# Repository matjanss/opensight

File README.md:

# OpenSights

An ESP32 (NodeMCU-32S) that talks Bluetooth LE to a desktop app written in Rust.

- **firmware/** — PlatformIO project for the ESP32
- **app/** — Rust/egui desktop app (Linux, macOS, Windows)
- **protocol/PROTOCOL.md** — the BLE protocol both sides implement
- **hardware/** — KiCad projects for the sensor hardware

Open `esp-sensor.code-workspace` in VS Code: PlatformIO picks up `firmware/` and
rust-analyzer picks up `app/`.

## What it does

- The sensor is the prototype of an electronic target: an acoustic target that locates
  each shot from the sound arriving at its microphones (being built, see
  [PLAN.md](PLAN.md) and [firmware/MEASUREMENT.md](firmware/MEASUREMENT.md)). Until the
  measuring hardware is running, a short press on BOOT makes a random test shot.
- The app shows the shots on a 10 m air pistol card and scores them: whole rings with X for an inner ten, or decimals (a setting). The series
  list and total sit next to the card.
- No shot is lost when the link drops or the sensor restarts: it keeps its shots in flash
  (about 2,000 of them) and resends the ones the app missed.
- A shot the sensor heard but couldn't measure (a second shot too soon after another), or
  one only the light curtain saw (through an existing hole), is listed in the series as
  "not scored", with a notice on the card: check the paper card for those. Click one (in
  the list or on the notice) to resolve it: place it on the card (click the hole, drag the
  shot until it fits, or type x and y), mark it the same hole as another shot, or count it a
  miss (0). It then takes its place in the series, marked "by hand", and can be changed or
  put back to "not scored" by selecting it.
- The app can save every event the sensor captured (also the rejected ones) to a log file,
  one per day, in the same format as the sensor's serial log (Settings → Measurement; on by
  default). Settings also show the sensor's calibration, settings and air readings.
- Settings → Measurement → **A shot needs the IR curtain's confirmation** switches the light
  curtain's check on the sensor on or off. Off, the sound alone decides what counts as a
  shot (the curtain's lights are off too, and no shots through an existing hole are
  reported). On again, it uses the window last set (45–100 µs if none was).
- Settings → Measurement → **Change the settings…** edits the sensor's measuring settings:
  the solver's limits, the curtain's window, the mic span, the dead time and the channels.
  Values out of range can't be written; the sensor's own check has the last word, and the
  app says when it didn't take them.
- Settings → **Shot highlight color** (blue or red): the ring drawn around the shot you
  click, and around the holes found in a card photo.
- The notices on the card (close calls, hits not scored) minimise with the bar at their top
  right, to just "!" and a short title; click that to open them again.
- Click on shots that overlap (a tight group, two shots through one hole) to get a list of
  them all; pick one to see its details.
- Calibrate from the app: Settings → Measurement → **Calibrate…** walks through the spark
  points of the calibration template (16 points, 10 sparks each), fits the microphones'
  positions and timing, shows the result, and writes it to the sensor. **Field check…** makes
  a few sparks at the template's centre and tells you whether the calibration still holds.
- **Take photo** (under the series): a photo of the shot card, taken with a phone, shows
  under the shots, and the app compares each shot with its hole (the sensor's accuracy).
  The series list then shows each shot's score on the paper beside the sensor's; **Card
  details** shows it all (the sensor against the holes per shot, warnings, shots per ring).
  **Finished** on the phone's page closes the app's link.
  Scan the QR code with the phone (on the same Wi-Fi), take the photo with the card flat and
  the phone straight above it. The photo's metadata (location and the like) is removed;
  photos are kept 30 days unless marked to keep. Work in progress, see
  [app/CARDPHOTO.md](app/CARDPHOTO.md).
- **Count cards** (the mode buttons at the top of the right column switch between
  **Shoot series** and **Count cards**; with or without a sensor): scores paper cards from
  photos, apart from the series. Scan the code once, then photograph card after card ("Upload
  another card", up to 20); the app counts them in turn and shows each card's holes and score,
  and the total, on the phone too. A hole the count missed can be added by hand (**Add a
  hole…**, click it on the card, Confirm), and one it found wrongly removed (× in its row,
  or Delete); a removed hole can be restored. **Start over** clears the cards.
- The dot in the status bar shows the link: green when connected, orange when connected
  but the sensor's heartbeat (every 2 s) has been missing for 6 s (it may have crashed),
  red when not connected. The blue LED only shows the sensor's status: pairing mode, a PIN reset, a shot.
- The sensor has a name (`OpenSights-xyz` at first) that you can change from the app.
- The app remembers the sensor and reconnects to it automatically.
- Pairing needs the sensor's 6-digit PIN (`000000` at first), which you can change from
  the app. Forgot it? Hold BOOT for 10 s: the PIN is reset and all computers are unpaired.

## Hardware

[hardware/acoustic-sensor/](hardware/acoustic-sensor/) is the first measuring board: one
acoustic channel with a MEMS microphone, a preamp, and two comparator thresholds,
connected to the host board through a 5-pin JST XH connector. Its
[README](hardware/acoustic-sensor/README.md) describes the board, the files and the checks
to do before ordering. The [schematic PDF](hardware/acoustic-sensor/mic_board_schematic.pdf)
can be read without KiCad. Open the project with KiCad 10 or newer.

[hardware/host-board/](hardware/host-board/) is the board the sensors plug into: the
NodeMCU-32S on sockets, 8 sensor connectors, the IR curtain, a DS18B20 and the panel LED
and button, all through-hole. Its [README](hardware/host-board/README.md) has the layout,
the GPIO map and assembly notes; the [schematic](hardware/host-board/host_board_schematic.pdf)
and [assembly drawing](hardware/host-board/host_board_assembly.pdf) are PDFs.

## Getting started

From source:

1. Flash the firmware: `pio run -d firmware -t upload`
2. Start the app: `cd app && cargo run`
3. Pair: hold **BOOT** for 2 s until the LED blinks fast, press **Pair** in the app, and
   enter the PIN (**000000**) when asked.

After pairing once, the app connects by itself whenever the sensor is in range.

## Downloads

Every version tag (`v0.1.0`, …) builds a GitHub Release with the app for Linux, Windows
and macOS and the firmware. The binaries aren't signed, so each system warns once:

- **Linux** (x86_64): unpack, then `./opensights-app`.
- **Windows 11**: unzip and start `opensights-app.exe`. SmartScreen says "Windows
  protected your PC": click **More info → Run anyway**.
- **macOS** (Apple Silicon and Intel): unzip and move **OpenSights.app** to Applications.
  The first start is blocked. Open **System Settings → Privacy & Security** and click
  **Open Anyway**, or run `xattr -dr com.apple.quarantine "/Applications/OpenSights.app"`.
  macOS then asks for Bluetooth access.
- **Firmware** (`pip install esptool`):
  - New board: `esptool.py --chip esp32 write_flash 0x0 opensights-firmware-…-full.bin`.
    This also erases the stored name, PIN and pairings.
  - Update, keeping name, PIN and pairings:
    `esptool.py --chip esp32 write_flash 0x10000 opensights-firmware-…-app.bin`.
  - The app and the firmware must speak the same protocol version (now 3): update both.
    After a firmware update, a Linux computer may keep the sensor's old Bluetooth layout:
    the app then asks you to pair again (hold BOOT for 2 s, press Pair).

To make a release: `git tag v0.1.0 && git push origin v0.1.0`.

## Notes per platform

- **Linux:** the app runs its own pairing agent and asks for the PIN in its own window,
  so no desktop Bluetooth settings are needed.
- **macOS:** a Bluetooth app must be a `.app` bundle with a Bluetooth usage description,
  or macOS refuses access. Running from a terminal uses the terminal's permission.
- **Card photos:** the phone reaches the app on port 8710 of this computer. A firewall may
  have to let it in (Windows asks the first time).
- **Windows:** if no PIN prompt appears, pair the sensor in Settings → Bluetooth while it
  is in pairing mode, then press Connect in the app.

## Forgetting a sensor

"Forget sensor" in the app stops automatic reconnects. The bond itself stays in your
operating system's Bluetooth settings; remove it there to pair from scratch.

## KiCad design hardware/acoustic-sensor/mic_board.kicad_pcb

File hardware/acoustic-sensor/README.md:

# Mic sensor board v0.3 (one acoustic channel)

GTA2718B-3 bottom-port MEMS mic → TLV9062 two-stage preamp (×6.3–17.7, ×12 at RV1 mid-travel, three 16 kHz high-pass poles) → TLV3202 dual comparator (VTH_L / VTH_H) → J1 to the host board.

## Files
- `mic_board.kicad_pro / .kicad_sch / .kicad_pcb`: KiCad project, KiCad 10 format (open it with KiCad 10 or newer).
- `mic_board.kicad_sym`, `mic_board.pretty/`: project-local symbols and the mic footprint (already in the project's sym-lib-table / fp-lib-table). All other footprints come from the standard KiCad libraries.
- `mic_board_schematic.pdf`: schematic.
- `mechanical/`: the board as STEP and STL for the holders, with the sizes that matter (see its README).
- `mic_board_parts_list.csv`: all parts incl. hand-fitted ones, with quantities for 5 boards.
- `production/`: the JLCPCB files from the Fabrication Toolkit plugin (options in `fabrication-toolkit-options.json`): `mic_board.zip` (gerbers + drill files), `bom.csv`, `positions.csv`, `designators.csv`, `netlist.ipc`. The BOM and positions also list the hand-fitted parts (J1, RV1–RV3, test points): leave those out of the JLC assembly order.

## Board
- 44 × 27 mm, 2 layers, **1.0 mm** FR-4 (set this when ordering), bottom layer = GND plane, top has a GND pour. No mounting holes: the board is clamped.
- No parts on top in the end strips (5.3 mm at the west end, 6.1 mm at the east end): room for the clamps.
- The board stands on its long edge. Bottom edge = paper side: mic port 5.5 mm from it. Flipped over: 21.5 mm. The holders put that edge on the paper, so the mic height h (PLAN D3) is 5.5 mm, the firmware default; a gap adds to it. The port is centred on the length (x = 22 mm), so it stays at the same place along the frame when the board is flipped.
- The 3D files and the sizes for the holders are in [mechanical/](mechanical/README.md).
- Sound enters through a 0.5 mm non-plated hole under the mic (bottom side, marked "MIC PORT"); the bottom plane and all signal tracks stay clear of it.
- J1: JST XH 5-pin vertical, **2.50 mm pitch**: 1 VA, 2 GND, 3 OUT_L, 4 GND, 5 OUT_H (labels on the bottom silkscreen).
- Test loops: SIG, VMID, GND (Keystone 5000-series, hand-fit). Test pads: VTH_L next to C5, VTH_H next to C6.
- Trimpots (Bourns 3296W, hand-fit): RV2 = low threshold, RV3 = high threshold, RV1 = gain.

## Checks done
- Schematic (wired, in blocks A–E like the project doc) = intended circuit (26 nets, 41 parts); PCB pads = schematic nets (96 pads), footprints linked to their symbols.
- DRC (KiCad 7 engine, JLC-friendly rules: 0.2 mm clearance, 0.25/0.4 mm tracks, 0.6/0.3 mm vias): 0 errors, 0 unconnected; the only warnings are "library not in this configuration" from the generating machine.

## Check before ordering
1. **Mic footprint: wrong, to fix before ordering** (checked 2026-11-23 against the
   GTA2718B-3 datasheet from LCSC, C50275772: Fig. 11 and "Recommended PCB and Stencil Design
   Pattern", p. 6 and 11). The GND ring (Ø0.95/1.45 mm) and the 0.5 mm hole are right
   (0.5–0.7 mm recommended). The signal pads are not:
   - **Pads 1 and 2 are mirrored, so VDD and OUTPUT are swapped.** The datasheet draws the
     pads in its bottom view (pin 1 left, pin 2 right, the port below); seen from the top, as
     a footprint is drawn, pin 1 is on the right, where the top view's polarity dot is. With
     the pads at +x of the port, as in this footprint, pin 1 belongs at **+y**; the footprint
     has pad 1 at −y. Check it in JLC's assembly preview too (item 2): MK1's pin-1 mark must
     sit on the VDD pad (the one to R1 and C1).
   - **Position and size:** the datasheet's pads are 0.65 × 0.545 mm (across × along the
     part), 0.95 mm apart (centres), their inner edge 1.205 mm from the port centre, so
     their centres at x = 1.4775, y = ±0.475 mm. The footprint has 0.65 × 0.65 mm pads at x
     = 1.6, y = ±0.6025 (1.205 mm apart): 0.12–0.13 mm out in each direction, about 70 % of
     each part pad on its land. The old note above read "1.6" (the pads' total span) and
     "1.205" (the port to the pads' edge) as other dimensions.
   - **Fixed 2026-11-23** in the footprint (`mic_board.pretty`) and its copy on the board:
     pad 1 at (1.4775, +0.475), pad 2 at (1.4775, −0.475), both 0.545 × 0.65 mm; the
     silkscreen dot at (2.25, +0.475), beside pad 1. The 3D model
     (`mic_board.3dshapes`) had the same pads and a GND ring of r 0.53–0.67 mm: now the
     datasheet's pads and r 0.475–0.725 mm. Its pin-1 dot (a recess in the lid) was at the
     old pad 1's corner (KiCad's 3D y points up, the footprint's down): moved to pad 1's,
     checked in KiCad's 3D render.
   - **VDD and OUT at MK1 re-routed** (the user, 2026-11-23) onto the moved pads. DRC
     (KiCad 10, `kicad-cli`, 2026-11-24): 0 errors, 0 unconnected pads, the 8 silkscreen
     warnings as before. The production files made again from it.
2. **JLC preview**: confirm the rotation of U1, U2 (pin 1 dot) and MK1 (pads towards U1, port towards J1). The CPL gives MK1 at its package centre (0.5 mm from the port).
3. **Routing**: a scripted first pass. Worth a look in KiCad, mainly around the mic/input (C2, R2, U1 pin 3) and the comparator outputs.
4. **ERC/DRC in KiCad 10** (2026-11-23, KiCad 10.0.8, `kicad-cli`): ERC 0 violations;
   schematic parity 0 issues. DRC: 2 clearance errors between the U1A + input track and the
   GND zone, which go away when the zones are refilled (a stale fill), and 8 silkscreen
   warnings. **Refill the zones (B) and save before making the Gerbers:** they carry the
   fill as saved.

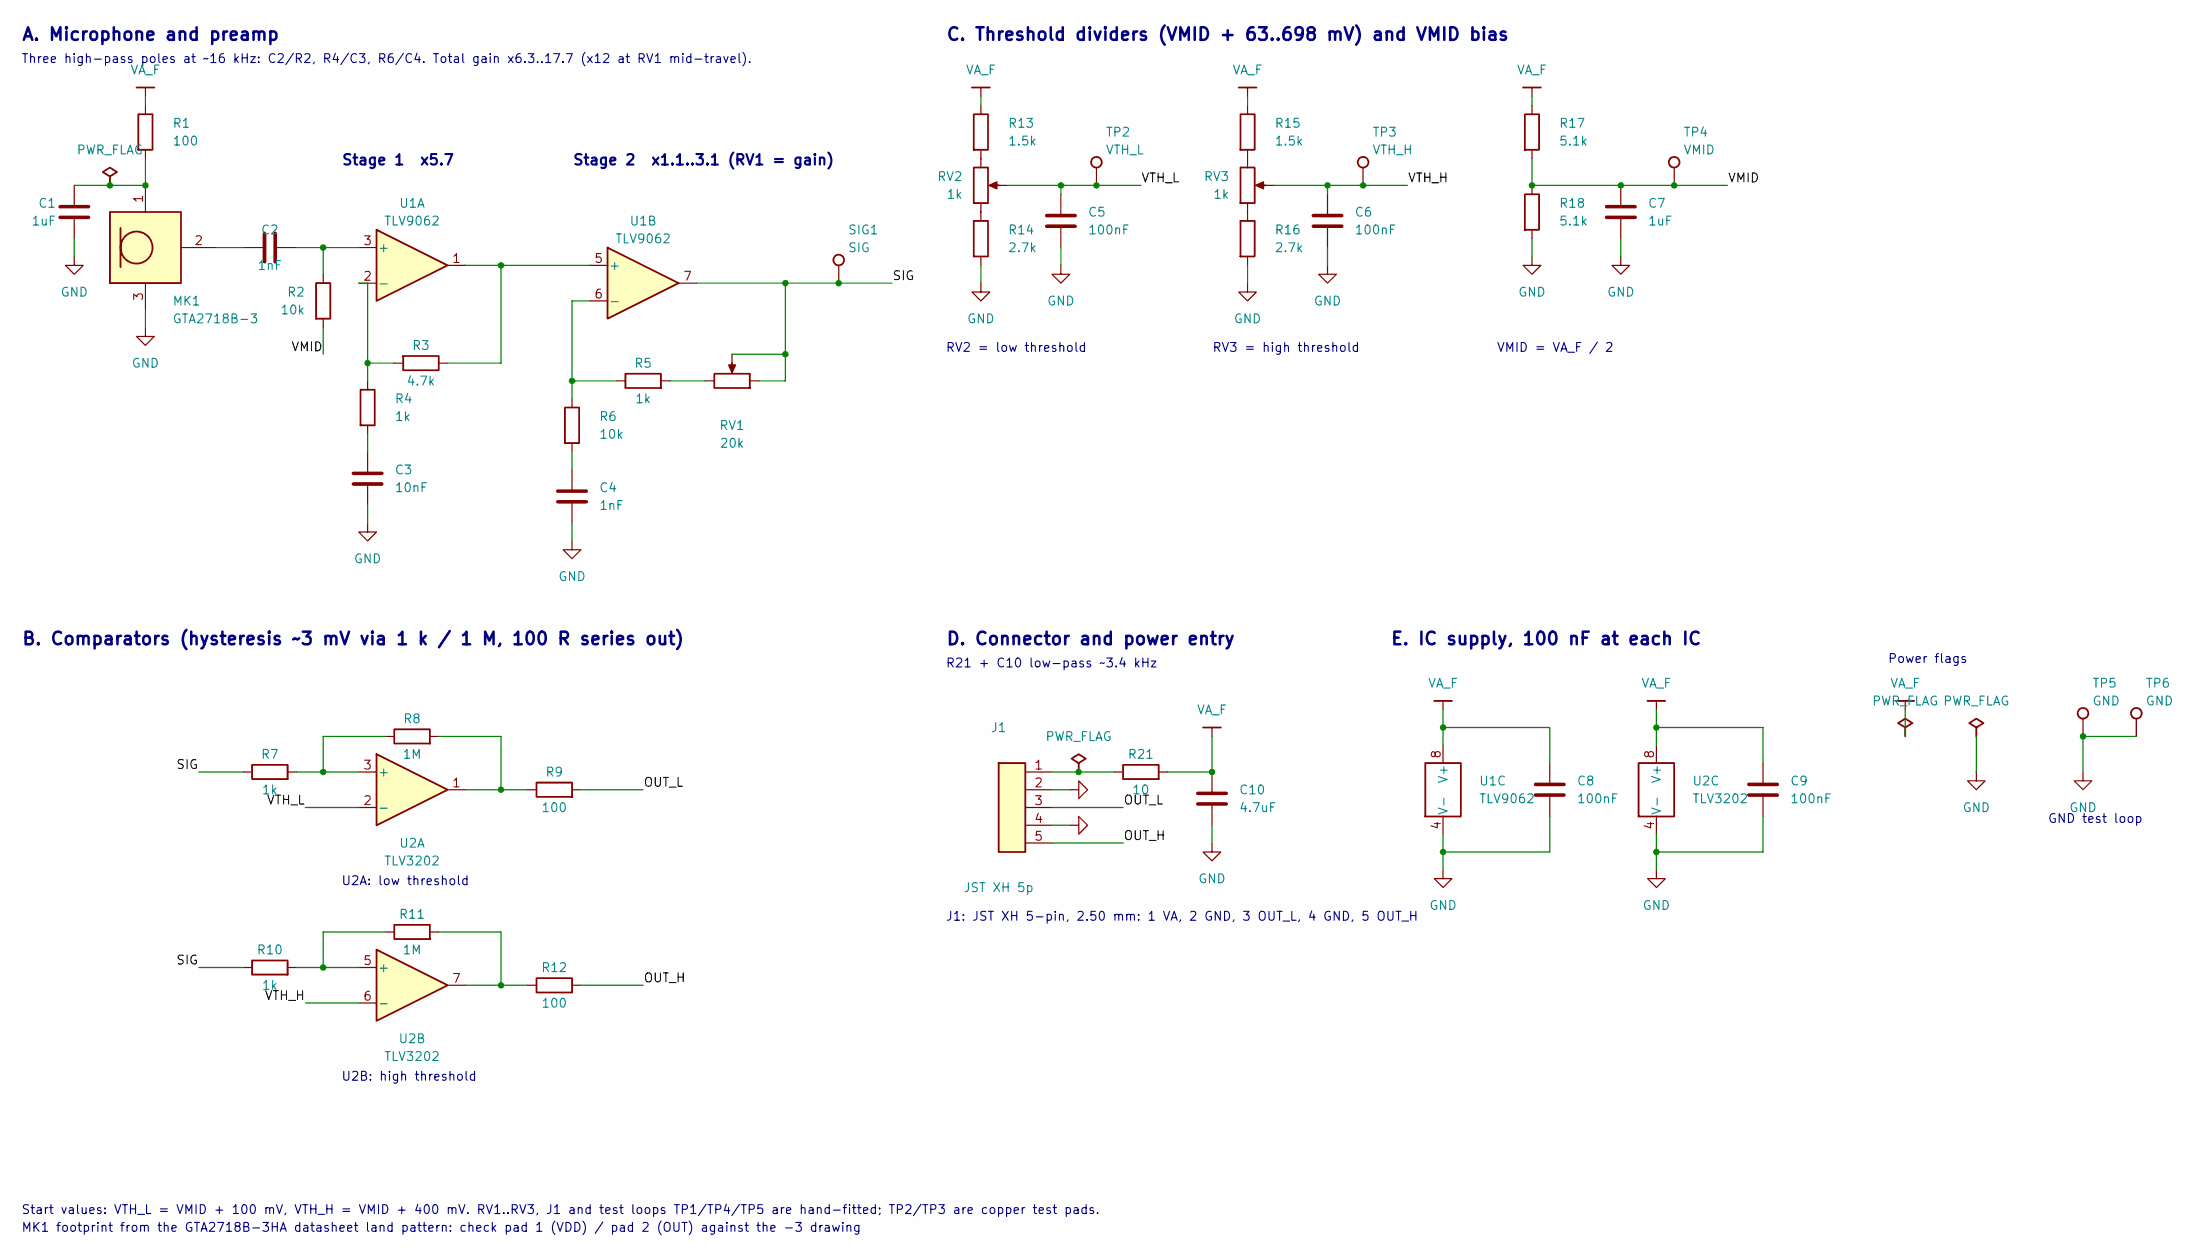
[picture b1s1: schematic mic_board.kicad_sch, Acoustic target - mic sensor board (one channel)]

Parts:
C1, C7: 1uF; C_0805_2012Metric; MPN CL21B105KBFNNNE; LCSC C28323
C2, C4: 1nF; C_0805_2012Metric; MPN CL21B102KBCNNNC; LCSC C46653
C3: 10nF; C_0805_2012Metric; MPN CL21B103KBANNNC; LCSC C1710
C5, C6, C8, C9: 100nF; C_0805_2012Metric; MPN CC0805KRX7R9BB104; LCSC C49678
C10: 4.7uF; C_0805_2012Metric; MPN CL21A475KAQNNNE; LCSC C1779
J1: JST XH 5p; JST_XH_B5B-XH-A_1x05_P2.50mm_Vertical; MPN B5B-XH-A
MK1: GTA2718B-3; MIC_GTA2718B_BottomPort_2.75x1.85mm; MPN GTA2718B-3; LCSC C50275772
R1, R9, R12: 100; R_0805_2012Metric; MPN 0805W8F1000T5E; LCSC C17408
R2, R6: 10k; R_0805_2012Metric; MPN 0805W8F1002T5E; LCSC C17414
R3: 4.7k; R_0805_2012Metric; MPN 0805W8F4701T5E; LCSC C17673
R4, R5, R7, R10: 1k; R_0805_2012Metric; MPN 0805W8F1001T5E; LCSC C17513
R8, R11: 1M; R_0805_2012Metric; MPN 0805W8F1004T5E; LCSC C17514
R13, R15: 1.5k; R_0805_2012Metric; MPN 0805W8F1501T5E; LCSC C4310
R14, R16: 2.7k; R_0805_2012Metric; MPN 0805W8F2701T5E; LCSC C17530
R17, R18: 5.1k; R_0805_2012Metric; MPN 0805W8F5101T5E; LCSC C27834
R21: 10; R_0805_2012Metric; MPN 0805W8F100JT5E; LCSC C17415
RV1: 20k; Potentiometer_Bourns_3296W_Vertical; MPN 3296W-1-203LF
RV2, RV3: 1k; Potentiometer_Bourns_3296W_Vertical; MPN 3296W-1-102LF
SIG1: SIG; TestPoint_Pad_D1.5mm; MPN Keystone 5000
TP2: VTH_L; TestPoint_Pad_D1.5mm; MPN test pad (copper only)
TP3: VTH_H; TestPoint_Pad_D1.5mm; MPN test pad (copper only)
TP4: VMID; TestPoint_Pad_D1.5mm; MPN Keystone 5000
TP5, TP6: GND; TestPoint_Keystone_5000-5004_Miniature; MPN Keystone 5000
U1: TLV9062; SOIC-8_3.9x4.9mm_P1.27mm; MPN TLV9062IDR; LCSC C398355
U2: TLV3202; SOIC-8_3.9x4.9mm_P1.27mm; MPN TLV3202AIDR; LCSC C129325

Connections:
/OUT_H: J1.5 (OUT_H), R12.2
/OUT_L: J1.3 (OUT_L), R9.2
/SIG: R7.1, R10.1, RV1.2, RV1.3, SIG1.1 (1_1), U1.7
/VMID: C7.1, R2.2, R17.2, R18.1, TP4.1 (1_1)
/VTH_H: C6.1, RV3.2, TP3.1 (1_1), U2.6 (-)
/VTH_L: C5.1, RV2.2, TP2.1 (1_1), U2.2 (-)
GND: C1.2, C3.2, C4.2, C5.2, C6.2, C7.2, C8.2, C9.2, C10.2, J1.2 (GND), J1.4 (GND), MK1.3 (GND), R14.2, R16.2, R18.2, TP5.1 (1_1), TP6.1 (1_1), U1.4 (V-), U2.4 (V-)
unnamed: C3.1, R4.2
unnamed: C4.1, R6.2
unnamed: J1.1 (VA), R21.1
unnamed: C2.1, MK1.2 (OUT)
unnamed: C1.1, MK1.1 (VDD), R1.2
unnamed: R5.2, RV1.1
unnamed: R8.2, R9.1, U2.1
unnamed: R11.2, R12.1, U2.7
unnamed: R13.2, RV2.1
unnamed: R14.1, RV2.3
unnamed: R15.2, RV3.1
unnamed: R16.1, RV3.3
unnamed: C2.2, R2.1, U1.3 (+)
unnamed: R3.2, R4.1, U1.2 (-)
unnamed: R3.1, U1.1, U1.5 (+)
unnamed: R5.1, R6.1, U1.6 (-)
unnamed: R7.2, R8.1, U2.3 (+)
unnamed: R10.2, R11.1, U2.5 (+)
VA_F: C8.1, C9.1, C10.1, R1.1, R13.1, R15.1, R17.1, R21.2, U1.8 (V+), U2.8 (V+)

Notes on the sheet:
Power flags
B. Comparators (hysteresis ~3 mV via 1 k / 1 M, 100 R series out)
RV2 = low threshold
A. Microphone and preamp
VMID = VA_F / 2
D. Connector and power entry
Start values: VTH_L = VMID + 100 mV, VTH_H = VMID + 400 mV. RV1..RV3, J1 and test loops TP1/TP4/TP5 are hand-fitted; TP2/TP3 are copper test pads.
R21 + C10 low-pass ~3.4 kHz
J1: JST XH 5-pin, 2.50 mm: 1 VA, 2 GND, 3 OUT_L, 4 GND, 5 OUT_H
RV3 = high threshold
C. Threshold dividers (VMID + 63..698 mV) and VMID bias
U2A: low threshold
E. IC supply, 100 nF at each IC
Three high-pass poles at ~16 kHz: C2/R2, R4/C3, R6/C4. Total gain x6.3..17.7 (x12 at RV1 mid-travel).
GND test loop
Stage 1 x5.7
MK1 footprint from the GTA2718B-3HA datasheet land pattern: check pad 1 (VDD) / pad 2 (OUT) against the -3 drawing
U2B: high threshold
Stage 2 x1.1..3.1 (RV1 = gain)

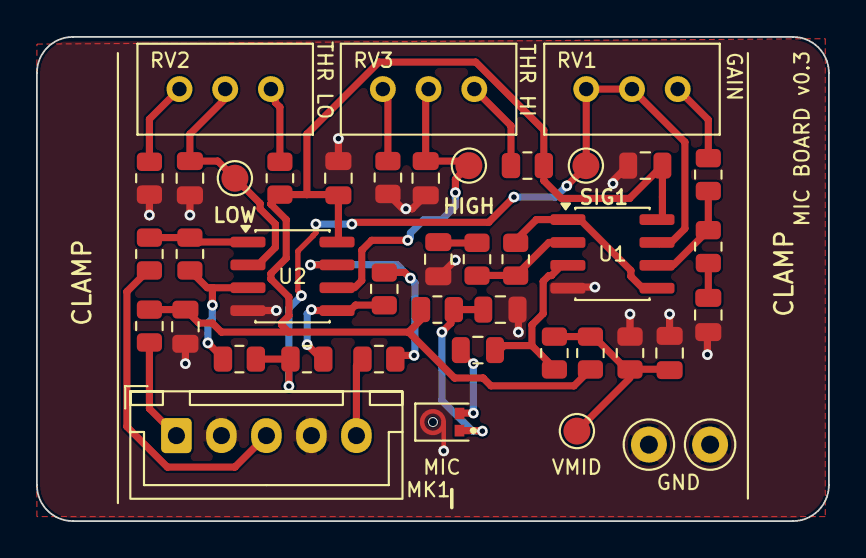
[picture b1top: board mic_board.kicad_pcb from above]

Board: 2 copper layers, 44.0 x 26.9 mm, 42 parts (0 on the bottom side), 26 nets.

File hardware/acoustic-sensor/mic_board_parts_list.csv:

Designator,Qty,Value,Description,Manufacturer part,LCSC,Footprint,Fitted by,Qty for 5 boards
"C1,C7",2,1u,Capacitor 1uF 50V X7R 0805,CL21B105KBFNNNE,C28323,C_0805_2012Metric,JLCPCB,10
"C2,C4",2,1n,Capacitor 1nF 50V X7R 0805,CL21B102KBCNNNC,C46653,C_0805_2012Metric,JLCPCB,10
C3,1,10n,Capacitor 10nF 50V X7R 0805,CL21B103KBANNNC,C1710,C_0805_2012Metric,JLCPCB,5
"C5,C6,C8,C9",4,100n,Capacitor 100nF 50V X7R 0805,CC0805KRX7R9BB104,C49678,C_0805_2012Metric,JLCPCB,20
C10,1,4.7u,Capacitor 4.7uF 25V X5R 0805,CL21A475KAQNNNE,C1779,C_0805_2012Metric,JLCPCB,5
J1,1,JST XH 5p,"JST XH 5-pin vertical, 2.50 mm",B5B-XH-A,,JST_XH_B5B-XH-A_1x05_P2.50mm_Vertical,hand,5
MK1,1,GTA2718B-3,"Analog MEMS mic, bottom port",GTA2718B-3,C50275772,MIC_GTA2718B_BottomPort_2.75x1.85mm,JLCPCB,5
"R1,R9,R12",3,100,Resistor 100Ω 1% 0805,0805W8F1000T5E,C17408,R_0805_2012Metric,JLCPCB,15
"R2,R6",2,10k,Resistor 10kΩ 1% 0805,0805W8F1002T5E,C17414,R_0805_2012Metric,JLCPCB,10
R3,1,4.7k,Resistor 4.7kΩ 1% 0805,0805W8F4701T5E,C17673,R_0805_2012Metric,JLCPCB,5
"R4,R5,R7,R10",4,1k,Resistor 1kΩ 1% 0805,0805W8F1001T5E,C17513,R_0805_2012Metric,JLCPCB,20
"R8,R11",2,1M,Resistor 1MΩ 1% 0805,0805W8F1004T5E,C17514,R_0805_2012Metric,JLCPCB,10
"R13,R15",2,1.5k,Resistor 1.5kΩ 1% 0805,0805W8F1501T5E,C4310,R_0805_2012Metric,JLCPCB,10
"R14,R16",2,2.7k,Resistor 2.7kΩ 1% 0805,0805W8F2701T5E,C17530,R_0805_2012Metric,JLCPCB,10
"R17,R18",2,5.1k,Resistor 5.1kΩ 1% 0805,0805W8F5101T5E,C27834,R_0805_2012Metric,JLCPCB,10
R21,1,10,Resistor 10Ω 1% 0805,0805W8F100JT5E,C17415,R_0805_2012Metric,JLCPCB,5
RV1,1,20k,Trimpot 25-turn top adjust,3296W-1-203LF,,Potentiometer_Bourns_3296W_Vertical,hand,5
"RV2,RV3",2,1k,Trimpot 25-turn top adjust,3296W-1-102LF,,Potentiometer_Bourns_3296W_Vertical,hand,10
"TP1,TP4,TP5",3,Keystone 5000,"Test loop, Keystone 5000-5004 (pick colours, e.g. 5001 black for GND)",Keystone 5000,,TestPoint_Keystone_5000-5004_Miniature,hand,15
"TP2,TP3",2,test pad (copper only),Test pad (copper only),test pad (copper only),,TestPoint_Pad_D1.5mm,none (copper),0
U1,1,TLV9062,Dual op-amp 10 MHz RRIO,TLV9062IDR,C398355,SOIC-8_3.9x4.9mm_P1.27mm,JLCPCB,5
U2,1,TLV3202,Dual comparator 40 ns push-pull,TLV3202AIDR,C129325,SOIC-8_3.9x4.9mm_P1.27mm,JLCPCB,5
